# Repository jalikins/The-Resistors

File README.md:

# The-Resistors
Contains all code for resistor sorter.

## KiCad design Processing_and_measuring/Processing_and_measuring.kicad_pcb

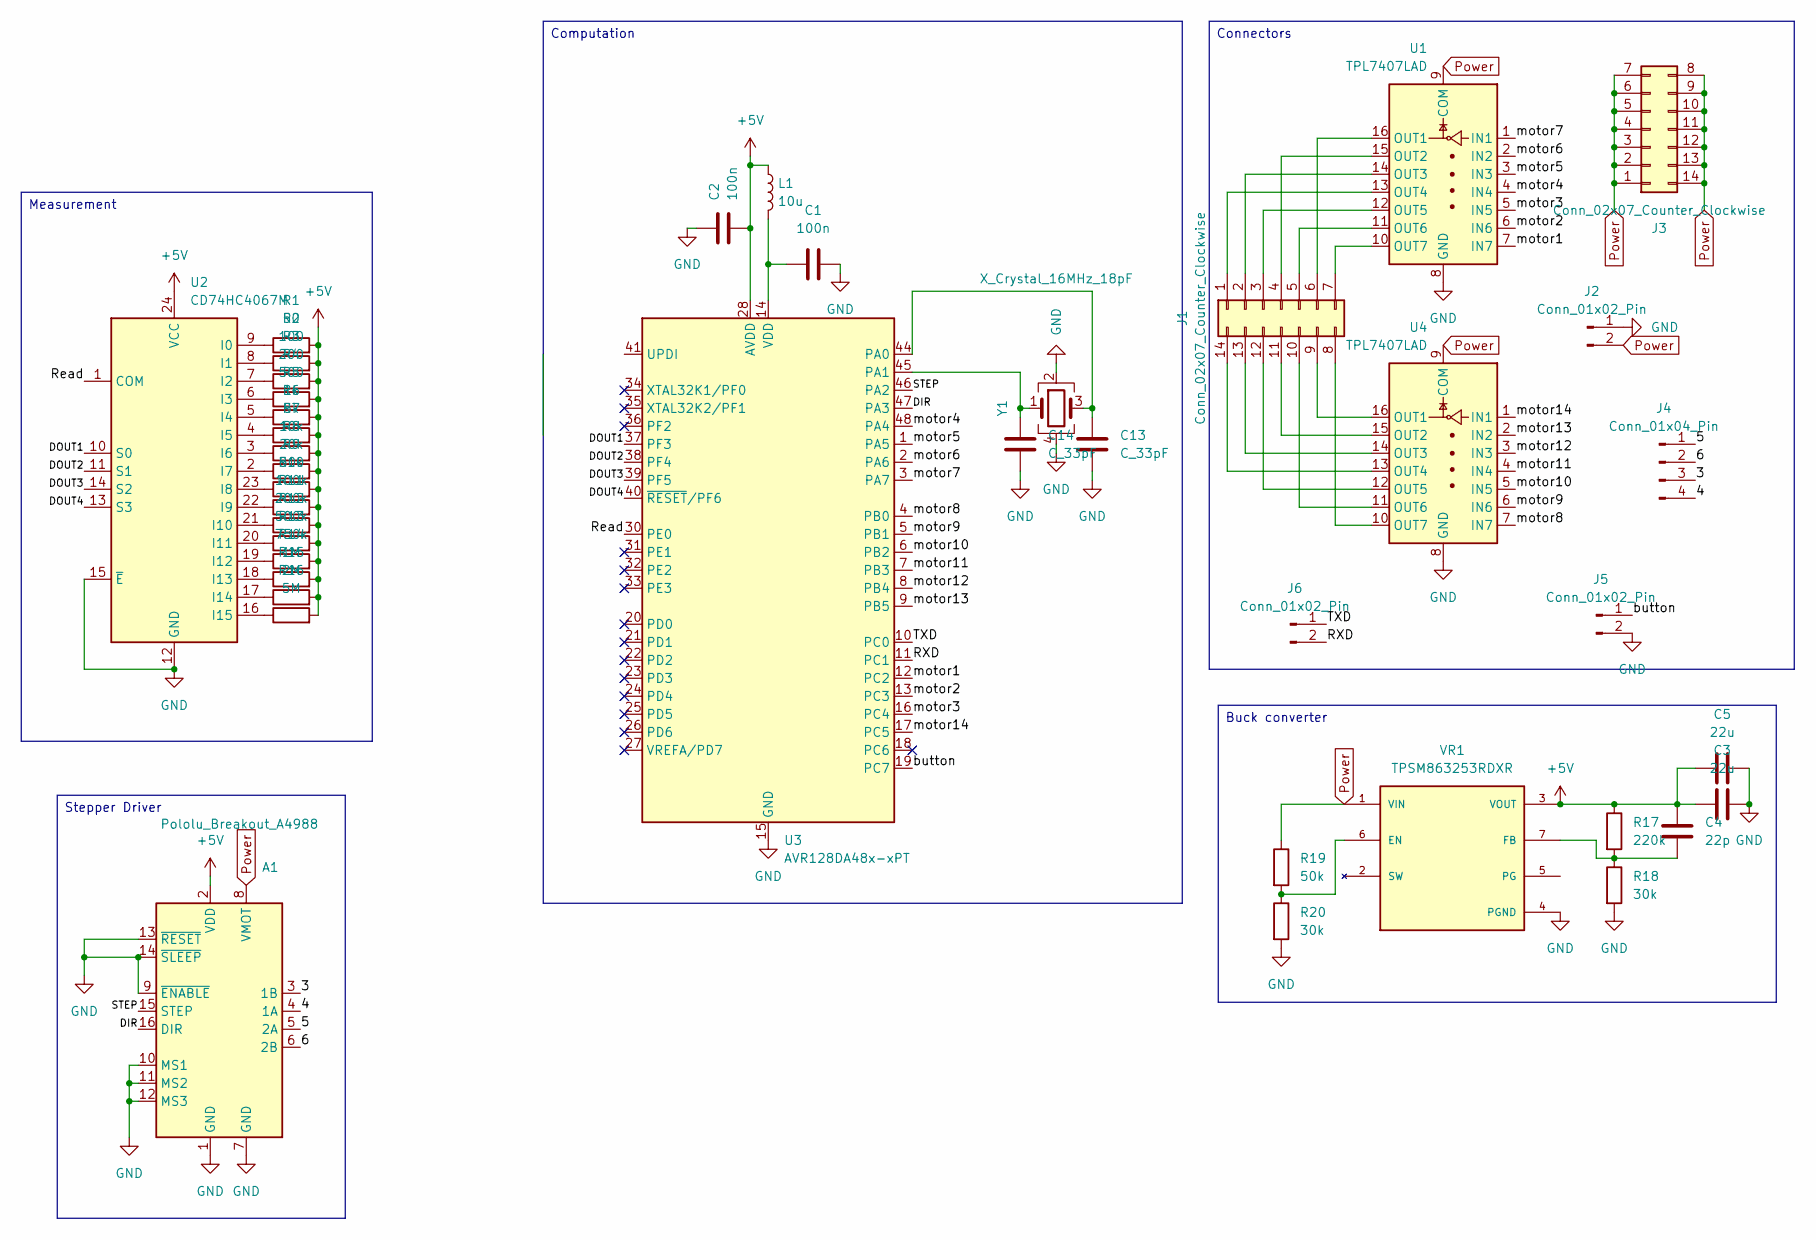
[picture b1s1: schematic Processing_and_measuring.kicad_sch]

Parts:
A1: Pololu_Breakout_A4988; Pololu_Breakout-16_15.2x20.3mm
C1, C2: 100n; C_0603_1608Metric
C3, C5: 22u; C_0603_1608Metric
C4: 22p; C_0603_1608Metric
C13, C14: C_33pF; C_0603_1608Metric; MPN CML0603C0G300JT50V
J1, J3: Conn_02x07_Counter_Clockwise; PinHeader_2x07_P2.54mm_Vertical
J2: Conn_01x02_Pin; AMASS_XT60IPW-M_1x03_P7.20mm_Horizontal
J4: Conn_01x04_Pin; PinHeader_1x04_P2.54mm_Vertical
J5, J6: Conn_01x02_Pin; PinHeader_1x02_P2.54mm_Vertical
L1: 10u; L_0603_1608Metric
R1: 50; R_0603_1608Metric
R2: 100; R_0603_1608Metric
R3: 200; R_0603_1608Metric
R4: 500; R_0603_1608Metric
R5: 1k; R_0603_1608Metric
R6: 5k; R_0603_1608Metric
R7: 10k; R_0603_1608Metric
R8: 20k; R_0603_1608Metric
R9, R19: 50k; R_0603_1608Metric
R10: 100k; R_0603_1608Metric
R11: 200k; R_0603_1608Metric
R12: 500k; R_0603_1608Metric
R13: 750k; R_0603_1608Metric
R14: 1M; R_0603_1608Metric
R15: 2M; R_0603_1608Metric
R16: 5M; R_0603_1608Metric
R17: 220k; R_0603_1608Metric
R18, R20: 30k; R_0603_1608Metric
U1, U4: TPL7407LAD; SOIC-16_3.9x9.9mm_P1.27mm
U2: CD74HC4067M; SOIC-24W_7.5x15.4mm_P1.27mm
U3: AVR128DA48x-xPT; TQFP-48_7x7mm_P0.5mm
VR1: TPSM863253RDXR; VREG_TPSM863253RDXR; PARTREV B
Y1: X_Crystal_16MHz_18pF; Crystal_TXC7M; MPN 7M-16.000MAAJ-T

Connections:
+5V: A1.2 (VDD), C2.2, C3.1, C4.1, C5.1, L1.1, R1.2, R2.2, R3.2, R4.2, R5.2, R6.2, R7.2, R8.2, R9.2, R10.2, R11.2, R12.2, R13.2, R14.2, R15.2, R16.2, R17.1, U2.24 (VCC), U3.28 (AVDD), VR1.3 (VOUT)
/3: A1.3 (1B), J4.3
/4: A1.4 (1A), J4.4
/5: A1.5 (2A), J4.1
/6: A1.6 (2B), J4.2
/DIR: A1.16 (DIR), U3.47 (PA3)
/DOUT1: U2.10 (S0), U3.37 (PF3)
/DOUT2: U2.11 (S1), U3.38 (PF4)
/DOUT3: U2.14 (S2), U3.39 (PF5)
/DOUT4: U2.13 (S3), U3.40 (~RESET/PF6)
/RXD: J6.2, U3.11 (PC1)
/Read: U2.1 (COM), U3.30 (PE0)
/STEP: A1.15 (STEP), U3.46 (PA2)
/TXD: J6.1, U3.10 (PC0)
/button: J5.1, U3.19 (PC7)
/motor1: U1.7 (IN7), U3.12 (PC2)
/motor2: U1.6 (IN6), U3.13 (PC3)
/motor3: U1.5 (IN5), U3.16 (PC4)
/motor4: U1.4 (IN4), U3.48 (PA4)
/motor5: U1.3 (IN3), U3.1 (PA5)
/motor6: U1.2 (IN2), U3.2 (PA6)
/motor7: U1.1 (IN1), U3.3 (PA7)
/motor8: U3.4 (PB0), U4.7 (IN7)
/motor9: U3.5 (PB1), U4.6 (IN6)
/motor10: U3.6 (PB2), U4.5 (IN5)
/motor11: U3.7 (PB3), U4.4 (IN4)
/motor12: U3.8 (PB4), U4.3 (IN3)
/motor13: U3.9 (PB5), U4.2 (IN2)
/motor14: U3.17 (PC5), U4.1 (IN1)
GND: A1.1 (GND), A1.7 (GND), A1.9 (~ENABLE), A1.10 (MS1), A1.11 (MS2), A1.12 (MS3), A1.13 (~RESET), A1.14 (~SLEEP), C1.2, C2.1, C3.2, C5.2, C13.2, C14.2, J2.1, J5.2, R18.2, R20.2, U1.8 (GND), U2.12 (GND), U2.15 (~E), U3.15 (GND), U3.29 (GND), U3.43 (GND), U4.8 (GND), VR1.4 (PGND), Y1.2, Y1.4
unnamed: C1.1, L1.2, U3.14 (VDD), U3.42 (VDD)
unnamed: J1.1, U1.13 (OUT4)
unnamed: J1.2, U1.14 (OUT3)
unnamed: J1.3, U1.12 (OUT5)
unnamed: J1.4, U1.15 (OUT2)
unnamed: J1.5, U1.11 (OUT6)
unnamed: J1.6, U1.16 (OUT1)
unnamed: J1.7, U1.10 (OUT7)
unnamed: J1.8, U4.10 (OUT7)
unnamed: J1.9, U4.16 (OUT1)
unnamed: J1.10, U4.11 (OUT6)
unnamed: J1.11, U4.15 (OUT2)
unnamed: J1.12, U4.12 (OUT5)
unnamed: J1.13, U4.14 (OUT3)
unnamed: J1.14, U4.13 (OUT4)
unnamed: R1.1, U2.9 (I0)
unnamed: R2.1, U2.8 (I1)
unnamed: R3.1, U2.7 (I2)
unnamed: R4.1, U2.6 (I3)
unnamed: R5.1, U2.5 (I4)
unnamed: R6.1, U2.4 (I5)
unnamed: R7.1, U2.3 (I6)
unnamed: R8.1, U2.2 (I7)
unnamed: R9.1, U2.23 (I8)
unnamed: R10.1, U2.22 (I9)
unnamed: R11.1, U2.21 (I10)
unnamed: R12.1, U2.20 (I11)
unnamed: R13.1, U2.19 (I12)
unnamed: R14.1, U2.18 (I13)
unnamed: R15.1, U2.17 (I14)
unnamed: R16.1, U2.16 (I15)
unnamed: C13.1, U3.44 (PA0), Y1.3
unnamed: C14.1, U3.45 (PA1), Y1.1
unnamed: R19.2, R20.1, VR1.6 (EN)
unnamed: C4.2, R17.2, R18.1, VR1.7 (FB)
Power: A1.8 (VMOT), J2.2, J3.1, J3.2, J3.3, J3.4, J3.5, J3.6, J3.7, J3.8, J3.9, J3.10, J3.11, J3.12, J3.13, J3.14, R19.1, U1.9 (COM), U4.9 (COM), VR1.1 (VIN)

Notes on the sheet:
Stepper Driver
Connectors
Buck converter
Measurement
Computation

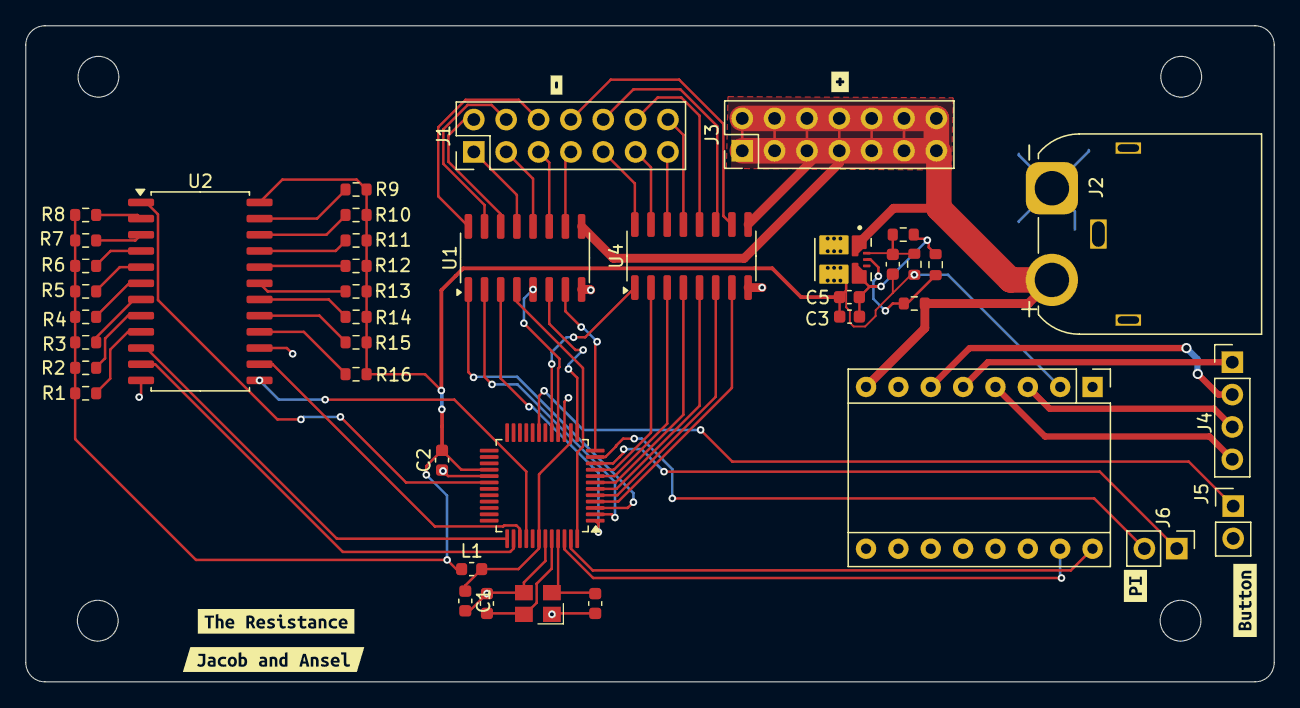
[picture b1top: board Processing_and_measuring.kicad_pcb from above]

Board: 2 copper layers, 98.0 x 51.5 mm, 47 parts (0 on the bottom side), 66 nets.

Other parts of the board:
kibuzzard-6920BB03: G***; kibuzzard-6920BB03
kibuzzard-6920BB24: G***; kibuzzard-6920BB24
kibuzzard-6920BBD9: G***; kibuzzard-6920BBD9
kibuzzard-6920BC10: G***; kibuzzard-6920BC10
kibuzzard-6920EC8A: G***; kibuzzard-6920EC8A
kibuzzard-6920EC74: G***; kibuzzard-6920EC74

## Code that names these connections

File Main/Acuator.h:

// has anything to do with the acutators



const uint8_t ACTUATORPIN [] = {
  PIN_PC2, // motor 1
  PIN_PC3, // motor 2
  PIN_PC4, // motor 3
  PIN_PA4, // motor 4
  PIN_PA5, // motor 5
  PIN_PA6, // motor 6 
  PIN_PA7, // motor 7
  PIN_PB0, // motor 8
  PIN_PB1, // motor 9
  PIN_PB2, // motor 10
  PIN_PB3, // motor 11
  PIN_PB4, // motor 12
  PIN_PB5, // motor 13
  PIN_PC5 // motor 14
};

const int NUM_ACTUAT = 14; // how many acutators we got

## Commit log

2025-11-04 Added code for sorting resistors
2025-11-11 Seperated into multiple files and updated code to work with mux
2025-11-11 set up of platformio and new workflow folders
2025-11-12 'Minor edits and improvements for extreme resistor values'
2025-11-14 pushing stepper motor test code
2025-11-14 Almost functional servo actuating code
2025-11-14 Comments and prep for integration
2025-11-14 Added stepper control
2025-11-14 Cleaned up code, assigned the remaining constants, and fixed errors by putting all functions in the header file with constants and variables
2025-11-16 testing stepper motor complete
2025-11-16 clean up of variable and ensure code is workin
2025-11-17 Incorperated working stepper motor code into main branch
2025-11-18 Added serial moniter commands along with minor debugging and testing
2025-11-20 KiCAd
2025-11-21 JacobIsTheGOATTTT
2025-11-21 added crystal and driver for steppers
2025-11-21 Buck converter
2025-11-21 Added footprints and connectors
2025-11-21 Started layout
2025-11-21 Connector for motor
2025-11-21 Layout work and power
2025-11-21 Addded footprint for buck converter
2025-11-21 More combining
2025-11-21 Corrected resistor footprints
2025-11-21 more changes to layout
2025-11-21 Updated capacitors and added button connector
2025-11-21 Lots of progress made on assembly
2025-11-21 Buck converter layout mostly
2025-11-21 Didn't save before last commit
2025-11-21 added button to mcu
2025-11-22 Fixing errors and warnings
2025-12-10 Added .ino files and updated code for pcb flashing
2025-12-12 adding initial user interface with customizable buttons
2025-12-12 adding Jekyll site configuration for website
2025-12-12 changing theme from minimal to cayman
2025-12-12 adding format overrides to make website honey-themed
2025-12-12 some edits to code
2025-12-14 code changes
2025-12-14 minor code fixes and implementation for external communication
2025-12-14 Added protothreading and fixed belt position iteration
2025-12-15 slight debug and initial system flash on PCB
2025-12-17 most up to date code
2025-12-17 fixed stall issues and click counter
2025-12-17 minor changes to timing
2025-12-17 adding the code correctly
2025-12-17 adding UI and bridging script
